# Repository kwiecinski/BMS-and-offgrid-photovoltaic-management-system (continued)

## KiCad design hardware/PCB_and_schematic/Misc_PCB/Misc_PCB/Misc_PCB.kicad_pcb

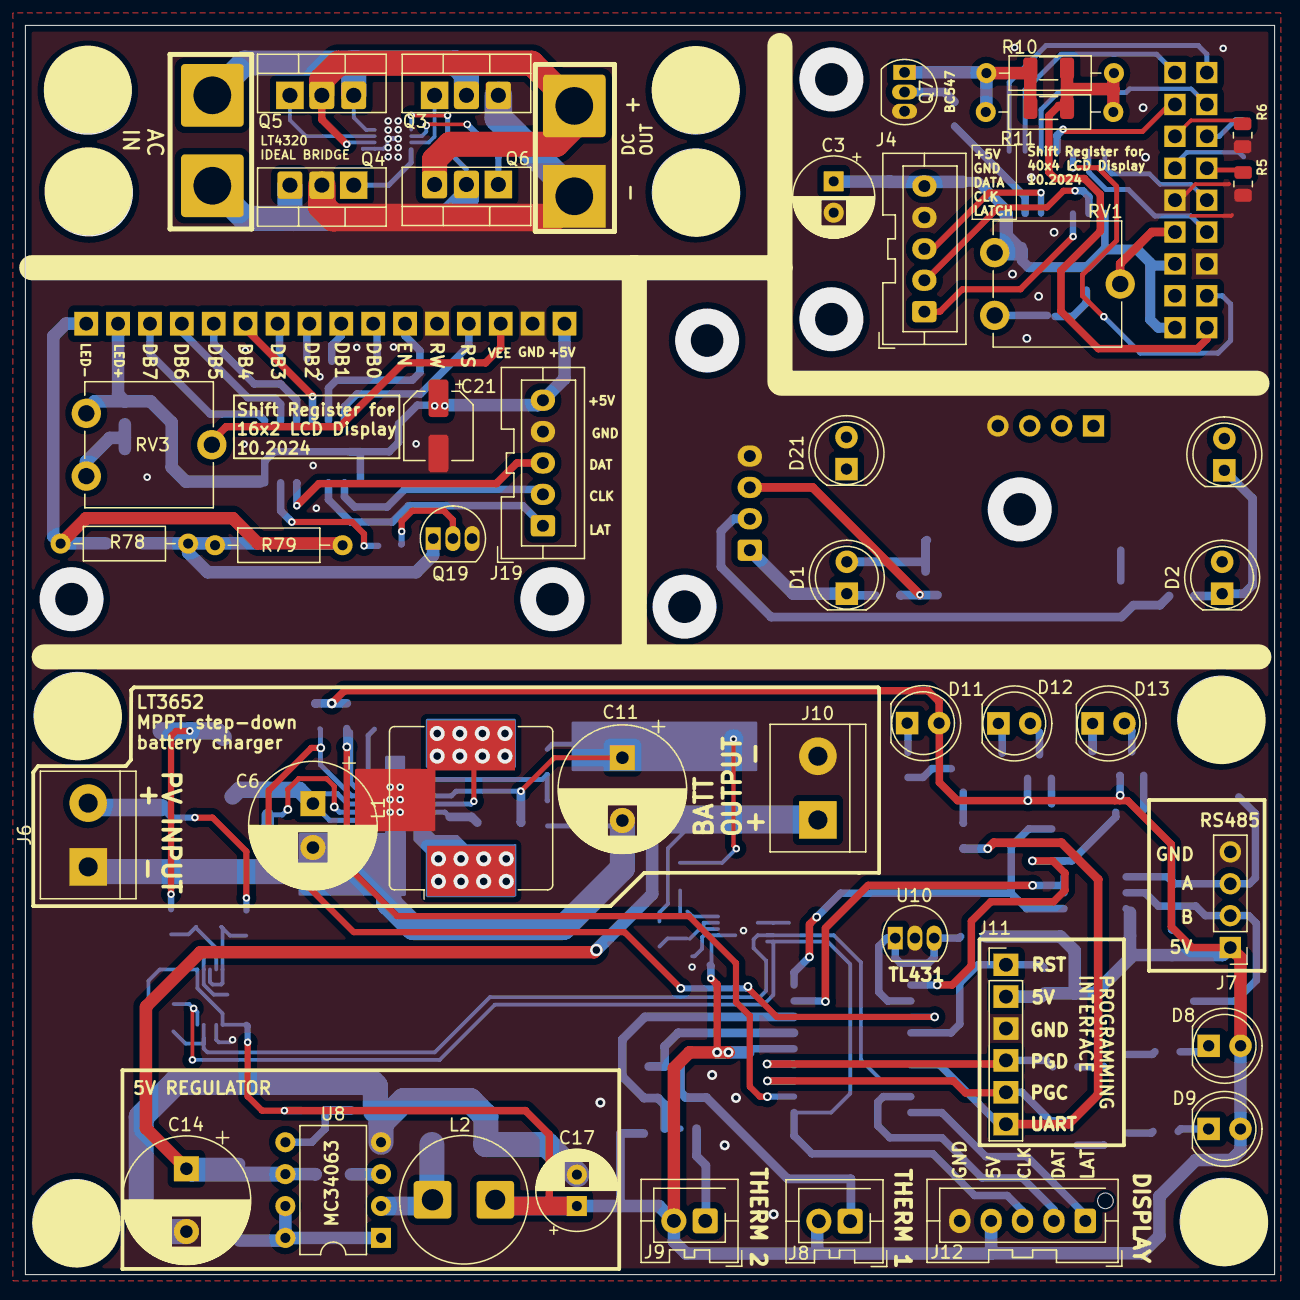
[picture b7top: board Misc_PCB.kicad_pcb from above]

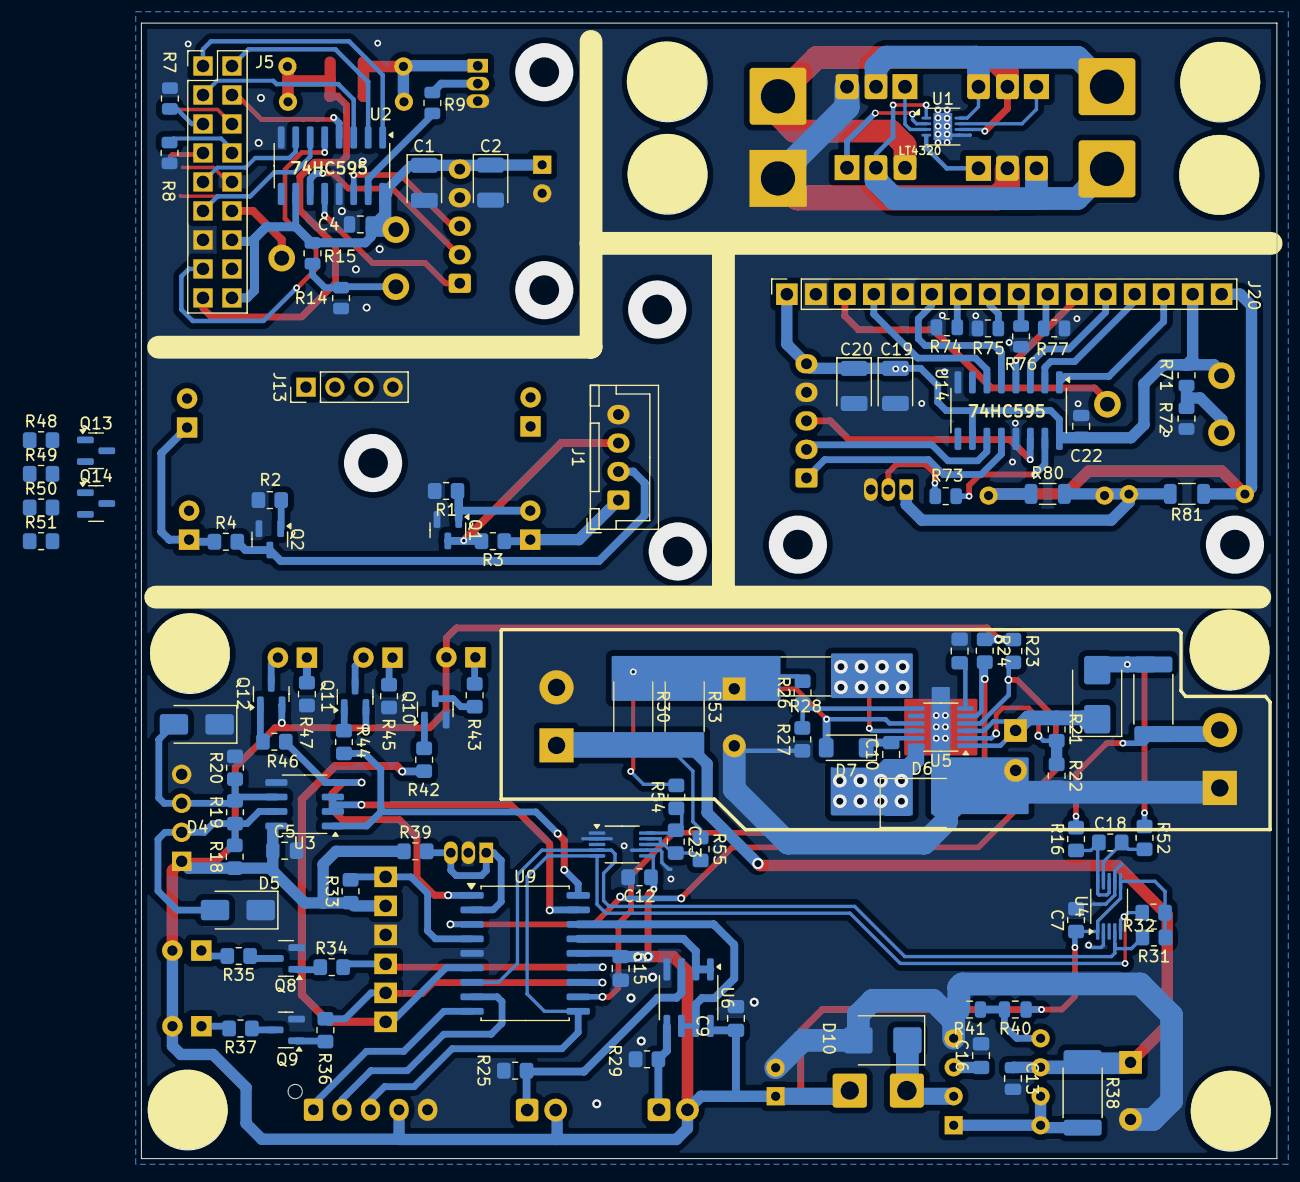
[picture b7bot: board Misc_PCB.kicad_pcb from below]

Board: 2 copper layers, 99.5 x 99.5 mm, 149 parts (103 on the bottom side), 110 nets.

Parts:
C1, C2, C19, C20: 470u/6,3V; CP_EIA-3528-21_Kemet-B
C3: 470u/6,3V; CP_Radial_D6.3mm_P2.50mm
C4, C13, C22: 100n; C_0805_2012Metric
C5, C9, C15: 100n; C_0805_2012Metric_Pad1.18x1.45mm_HandSolder
C6: 470u/40V; CP_Radial_D10.0mm_P3.50mm
C7, C12, C18, C23: 100n; R_0805_2012Metric_Pad1.20x1.40mm_HandSolder
C8: 0R; C_0805_2012Metric_Pad1.18x1.45mm_HandSolder
C10: 1u/10V; C_0805_2012Metric_Pad1.18x1.45mm_HandSolder
C11: 470u/16V; CP_Radial_D10.0mm_P5.00mm
C14: 670u/35V; CP_Radial_D10.0mm_P5.00mm
C16: 100p; C_0805_2012Metric_Pad1.18x1.45mm_HandSolder
C17: 560u/6,3V; CP_Radial_D6.3mm_P2.50mm
C21: 470u/6,3V; CP_Elec_5x5.7
D1, D2, D20, D21: BPV10; LED_D5.0mm
D3, D6, D10: D_Schottky; D_SMB
D4, D5: D_TVS; D_SMA
D7: 1N4148; D_MiniMELF
D8, D9, D11, D12, D13: LED; LED_D5.0mm
J1: DIODE_BLINK_METER; JST_XH_B4B-XH-A_1x04_P2.50mm_Vertical
J2: AC_IN; SolderWire-2.5sqmm_1x02_P7.2mm_D2.4mm_OD3.6mm
J3: DC_OUT; SolderWire-2.5sqmm_1x02_P7.2mm_D2.4mm_OD3.6mm
J4, J19: LCD_CONN; JST_XA_B05B-XASK-1_1x05_P2.50mm_Vertical
J5: LCD_DISPLAY; PinHeader_2x09_P2.54mm_Vertical
J6: SOLAR_PANEL; TerminalBlock_bornier-2_P5.08mm
J7: RS485; PinHeader_1x04_P2.54mm_Vertical
J8, J9: THERMISTOR; JST_XA_B02B-XASK-1-A_1x02_P2.50mm_Vertical
J10: BATT; TerminalBlock_bornier-2_P5.08mm
J11: ICP; PinHeader_1x06_P2.54mm_Vertical
J12: LCD_DISPLAY; JST_XA_B05B-XASK-1-A_1x05_P2.50mm_Vertical
J13: DIODE_BLINK_METER_OUT; PinHeader_1x04_P2.54mm_Vertical
J20: LCD16x2; PinSocket_1x16_P2.54mm_Vertical
L1: L; L_Bourns_SRR1208_12.7x12.7mm
L2: 220uH; L_Radial_D10.0mm_P5.00mm_Fastron_07P
Q1, Q2, Q8, Q9, Q10, Q13, Q14: BC817; SOT-23
Q3, Q4, Q5, Q6: IRF540N; TO-220-3_Vertical-little-bigger pads
Q7, Q19: BC547; TO-92_Inline_LITTLE_BIGGER
Q11, Q12: BC807; SOT-23
R1, R2, R48, R49: 47k; R_0805_2012Metric_Pad1.20x1.40mm_HandSolder
R3, R4, R50, R51: 22k; R_0805_2012Metric_Pad1.20x1.40mm_HandSolder
R5, R6, R7, R8, R9, R15, R71, R73, R74, R75, R76, R77: 10k; R_0805_2012Metric
R10, R11, R78, R79: R; R_Axial_DIN0207_L6.3mm_D2.5mm_P10.16mm_Horizontal
R12, R13, R80, R81: R; R_1206_3216Metric
R14, R72: 39k; R_0805_2012Metric
R16, R52, R54, R55: 10R; R_0805_2012Metric_Pad1.20x1.40mm_HandSolder
R17, R30: 50m; R_2512_6332Metric_Pad1.40x3.35mm_HandSolder
R18, R20, R21, R22: 510R; R_0805_2012Metric_Pad1.20x1.40mm_HandSolder
R19: 120R; R_0805_2012Metric_Pad1.20x1.40mm_HandSolder
R23, R24, R31, R32, R33: 10k; R_0805_2012Metric_Pad1.20x1.40mm_HandSolder
R25, R29: 100K; R_0805_2012Metric_Pad1.20x1.40mm_HandSolder
R26, R27: 100k; R_0805_2012Metric_Pad1.20x1.40mm_HandSolder
R28: 50mR; R_2512_6332Metric_Pad1.40x3.35mm_HandSolder
R34, R36, R42, R44, R46: 10K; R_0805_2012Metric_Pad1.20x1.40mm_HandSolder
R35, R37, R43, R45, R47: 220R; R_0805_2012Metric_Pad1.20x1.40mm_HandSolder
R38: 500m; R_2512_6332Metric_Pad1.40x3.35mm_HandSolder
R39: 1k; R_0805_2012Metric_Pad1.20x1.40mm_HandSolder
R40: 10k; C_0805_2012Metric
R41: 3k3; C_0805_2012Metric
R53: 100m; R_2512_6332Metric_Pad1.40x3.35mm_HandSolder
RV1, RV3: 10k; Potentiometer_ACP_CA9-V10_Vertical
U1: LT4320xDD-1; DFN-8-1EP_3x3mm_P0.5mm_EP1.65x2.38mm
U2, U14: 74HC595; SOIC-16_3.9x9.9mm_P1.27mm
U3: ST485; SOIC-8_3.9x4.9mm_P1.27mm
U4, U7: INA226; VSSOP-10_3x3mm_P0.5mm
U5: LT3652EMSE; MSOP-12-1EP_3x4mm_P0.65mm_EP1.65x2.85mm
U6: LM358; SOIC-8_3.9x4.9mm_P1.27mm
U8: MC34063AP; DIP-8_W7.62mm
U9: PIC16F819-ISO; SOIC-18W_7.5x11.6mm_P1.27mm
U10: TL431LP; TO-92_Inline_LITTLE_BIGGER

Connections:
+5V: C1.1, C2.1, C3.1, C4.1, C5.1, C7.1, C9.1, C12.1, C15.1, C17.1, C19.1, C20.1, C21.1, C22.1, D1.1 (K), D2.1 (K), D8.2 (A), D9.2 (A), D11.2 (A), D20.1 (K), D21.1 (K), J1.1, J4.5, J5.14, J5.18, J7.1, J8.2, J9.2, J11.2, J12.4, J13.1, J19.5, J20.1, J20.15, L2.2, Q11.2 (E), Q12.2 (E), R3.1, R4.1, R15.2, R18.1, R23.1, R24.1, R31.1, R32.1, R33.1, R39.1, R40.1, R50.1, R51.1, R71.2, RV1.3, RV3.3, U2.10 (~SRCLR), U2.16 (VCC), U3.8 (VCC), U4.1 (A1), U4.6 (VS), U6.8 (V+), U7.6 (VS), U9.14 (VDD), U14.10 (~SRCLR), U14.16 (VCC)
/LT3652 MPPT/RS485_A: D4.2 (A2), J7.3, R19.2, R20.1, U3.6 (A)
/LT3652 MPPT/RS485_B: D5.2 (A2), J7.2, R18.2, R19.1, U3.7 (B)
/Shift Register for 16x2 LCD Display/CLK: J19.2, U14.11 (SRCLK)
/Shift Register for 16x2 LCD Display/DATA: J19.3, U14.14 (SER)
/Shift Register for 16x2 LCD Display/LATCH: J19.1, U14.12 (RCLK)
/Shift Register for 40x4 LCD Display/CLK: J4.2, U2.11 (SRCLK)
/Shift Register for 40x4 LCD Display/DATA: J4.3, U2.14 (SER)
/Shift Register for 40x4 LCD Display/LATCH: J4.1, U2.12 (RCLK)
BACKLIGHT_DRIVE: R9.1, U2.15 (QA)
BACKLIGHT_DRIVE_A: R73.1, U14.15 (QA)
BATT_CURRENT_HIGH: C11.1, D7.2 (A), R26.2, R28.2, R30.1, R53.1, R54.2, U5.9 (BAT)
BATT_CURRENT_LOW: C13.1, C14.1, J10.1, R30.2, R38.1, R53.2, R55.1, U8.6 (Vin)
CHRG: R23.2, U5.4 (~CHRG), U9.3 (T0CKL/AN4/RA4)
DATA: J12.2, U9.8 (RB2/SDO/CCP1)
DB0: J5.8, R8.2
DB1: J5.7, R5.2
DB2: J5.6, R6.2
DB3: J5.5, R7.2
DB4: J5.4, U2.4 (QE)
DB4_A: J20.11, U14.4 (QE)
DB5: J5.3, U2.3 (QD)
DB5_A: J20.12, U14.3 (QD)
DB6: J5.2, U2.2 (QC)
DB6_A: J20.13, U14.2 (QC)
DB7: J5.1, U2.1 (QB)
DB7_A: J20.14, U14.1 (QB)
DBG_UART: J11.6, R42.2, U9.6 (RB0/INT)
E1: J5.9, U2.7 (QH)
E2: J5.15, U2.5 (QF)
EN: J20.6, U14.5 (QF)
FAULT: R24.2, U5.5 (~FAULT), U9.11 (RB5/~SS)
GND: C1.2, C2.2, C3.2, C4.2, C5.2, C6.2, C7.2, C8.2, C9.2, C11.2, C12.2, C13.2, C14.2, C15.2, C16.2, C17.2, C19.2, C20.2, C21.2, C22.2, D4.1 (A1), D5.1 (A1), D6.2 (A), D10.2 (A), J1.4, J3.2, J4.4, J5.10, J5.13, J6.1, J7.4, J10.2, J11.3, J12.5, J13.4, J19.4, J20.2, J20.5, Q1.2 (E), Q2.2 (E), Q3.3 (S), Q4.2 (D), Q7.3 (E), Q8.2 (E), Q9.2 (E), Q10.2 (E), Q13.2 (E), Q14.2 (E), Q19.3 (E), R1.2, R2.2, R5.1, R6.1, R7.1, R8.1, R14.2, R20.2, R22.2, R25.2, R27.1, R29.2, R41.2, R45.1, R47.1, R48.2, R49.2, R72.2, R74.1, R75.1, R76.1, R77.1, U1.5 (OUTN), U1.9 (OUTN), U2.8 (GND), U2.13 (~OE), U3.5 (GND), U4.2 (A0), U4.7 (GND), U5.13 (GND), U6.4 (V-), U7.1 (A1), U7.2 (A0), U7.7 (GND), U8.4 (GND), U9.5 (VSS), U10.2 (A), U14.8 (GND), U14.13 (~OE)
LATCH: J12.1, U9.9 (RB3/CCP1/PGM)
unnamed: D1.2 (A), Q1.1 (B), R1.1
unnamed: D2.2 (A), Q2.1 (B), R2.1
unnamed: C6.1, D3.1 (K), R21.1, U5.1 (V_{IN}), U5.3 (~SHDN)
unnamed: C10.1, D6.1 (K), L1.1, U5.12 (SW)
unnamed: C10.2, D7.1 (K), U5.11 (BOOST)
unnamed: D8.1 (K), R35.2
unnamed: D9.1 (K), R37.2
unnamed: D10.1 (K), L2.1, U8.2 (SwE)
unnamed: D11.1 (K), R43.2
unnamed: D12.2 (A), Q11.3 (C)
unnamed: D12.1 (K), R45.2
unnamed: D13.2 (A), Q12.3 (C)
unnamed: D13.1 (K), R47.2
unnamed: D20.2 (A), Q13.1 (B), R48.1
unnamed: D21.2 (A), Q14.1 (B), R49.1
unnamed: J1.2, Q2.3 (C), R4.2
unnamed: J1.3, Q1.3 (C), R3.2
unnamed: J2.1, Q4.3 (S), Q6.2 (D), U1.1 (IN2)
unnamed: J2.2, Q3.2 (D), Q5.3 (S), U1.8 (IN1)
unnamed: J3.1, Q5.2 (D), Q6.3 (S), U1.6 (OUTP)
unnamed: J5.12, RV1.2
unnamed: J5.17, R10.1, R11.1, R12.1, R13.1
unnamed: J8.1, R25.1, U6.3 (+)
unnamed: J9.1, R29.1, U6.5 (+)
unnamed: J13.2, Q14.3 (C), R51.2
unnamed: J13.3, Q13.3 (C), R50.2
unnamed: J20.3, RV3.2
unnamed: J20.7, R74.2
unnamed: J20.8, R75.2
unnamed: J20.9, R76.2
unnamed: J20.10, R77.2
unnamed: J20.16, R78.1, R79.1, R80.1, R81.1
unnamed: Q3.1 (G), U1.3 (BG2)
unnamed: Q4.1 (G), U1.4 (BG1)
unnamed: Q5.1 (G), U1.7 (TG1)
unnamed: Q6.1 (G), U1.2 (TG2)
unnamed: Q7.2 (B), R9.2
unnamed: Q7.1 (C), R10.2, R11.2, R12.2, R13.2
unnamed: Q8.1 (B), R34.1
unnamed: Q8.3 (C), R35.1
unnamed: Q9.1 (B), R36.1
unnamed: Q9.3 (C), R37.1
unnamed: Q10.1 (B), R42.1
unnamed: Q10.3 (C), R43.1
unnamed: Q11.1 (B), R44.1
unnamed: Q12.1 (B), R46.1
unnamed: Q19.2 (B), R73.2
unnamed: Q19.1 (C), R78.2, R79.2, R80.2, R81.2
unnamed: R14.1, R15.1, RV1.1
unnamed: R71.1, R72.1, RV3.1
unnamed: C18.1, R16.1, U4.8 (Vbus), U4.10 (Vin+)
unnamed: C18.2, R52.2, U4.9 (Vin-)
unnamed: L1.2, R28.1, U5.10 (SENSE)
unnamed: C8.1, U5.6 (TIMER)
unnamed: R26.1, R27.2, U5.7 (V_{FB})
unnamed: R21.2, R22.1, U5.2 (V_{IN_REG})
unnamed: C23.2, R55.2, U7.8 (Vbus), U7.9 (Vin-)
unnamed: C23.1, R54.1, U7.10 (Vin+)
unnamed: R38.2, U8.1 (SwC), U8.7 (Ipk), U8.8 (DC)
unnamed: C16.1, U8.3 (TC)
unnamed: R40.2, R41.1, U8.5 (Vfb)
PGC: J11.5, R36.2, U9.12 (RB6/T1OSO/T1CKI/PGC)
PGD: J11.4, R34.2, U9.13 (RB7/T1OSI/PGD)
RS: J5.11, U2.6 (QG)
RS232_RX: R44.2, U3.1 (RO), U9.18 (AN1/RA1)
RS232_TX: R46.2, U3.4 (DI), U9.1 (Vref-/AN2/RA2)
RS485_OUTPUT_ENABLE: U3.2 (~RE), U3.3 (DE), U9.17 (AN0/RA0)
RST: J11.1, R33.2, U9.4 (Vpp/~MCLR/RA5)
RS_A: J20.4, U14.6 (QG)
SCL_SCK: J12.3, R32.2, U4.5 (SCL), U7.5 (SCL), U9.10 (RB4/SCK/SCL)
SDA: R31.2, U4.4 (SDA), U7.4 (SDA), U9.7 (RB1/SDI/SDA)
SOLAR_CURRENT_HIGH: J6.2, R16.2, R17.1
SOLAR_CURRENT_LOW: D3.2 (A), R17.2, R52.1
TEMP1: U6.1, U6.2 (-), U9.15 (CLKO/OSC2/RA6)
TEMP2: U6.6 (-), U6.7, U9.16 (CLKI/OSC1/RA7)
VREF_2V5: R39.2, U9.2 (Vref+/AN3/RA3), U10.1 (REF), U10.3 (K)

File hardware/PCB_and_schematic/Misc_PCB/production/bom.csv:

Designator,Footprint,Quantity,Value,LCSC Part #
"C1, C19, C2, C20",CP_EIA-3528-21_Kemet-B,4,"470u/6,3V",
C10,0805,1,1u/10V,
C11,CP_Radial_D10.0mm_P5.00mm,1,470u/16V,
"C12, C13, C15, C18, C22, C23, C4, C5, C7, C9",0805,10,100n,
C14,CP_Radial_D10.0mm_P5.00mm,1,670u/35V,
C16,0805,1,100p,
C17,CP_Radial_D6.3mm_P2.50mm,1,"560u/6,3V",
C21,CP_Elec_5x5.7,1,"470u/6,3V",
C3,CP_Radial_D6.3mm_P2.50mm,1,"470u/6,3V",
C6,CP_Radial_D10.0mm_P3.50mm,1,470u/40V,
C8,0805,1,0R,
"D1, D2, D20, D21",LED_D5.0mm,4,BPV10,
"D10, D3, D6",D_SMB,3,D_Schottky,
"D11, D12, D13, D8, D9",LED_D5.0mm,5,LED,
"D4, D5",D_SMA,2,D_TVS,
D7,D_MiniMELF,1,1N4148,
J1,JST_XH_B4B-XH-A_1x04_P2.50mm_Vertical,1,DIODE_BLINK_METER,
J10,TerminalBlock_bornier-2_P5.08mm,1,BATT,
J11,PinHeader_1x06_P2.54mm_Vertical,1,ICP,
J12,JST_XA_B05B-XASK-1-A_1x05_P2.50mm_Vertical,1,LCD_DISPLAY,
J13,PinHeader_1x04_P2.54mm_Vertical,1,DIODE_BLINK_METER_OUT,
"J19, J4",JST_XA_B05B-XASK-1_1x05_P2.50mm_Vertical,2,LCD_CONN,
J2,SolderWire-2.5sqmm_1x02_P7.2mm_D2.4mm_OD3.6mm,1,AC_IN,
J20,PinSocket_1x16_P2.54mm_Vertical,1,LCD16x2,
J3,SolderWire-2.5sqmm_1x02_P7.2mm_D2.4mm_OD3.6mm,1,DC_OUT,
J5,PinHeader_2x09_P2.54mm_Vertical,1,LCD_DISPLAY,
J6,TerminalBlock_bornier-2_P5.08mm,1,SOLAR_PANEL,
J7,PinHeader_1x04_P2.54mm_Vertical,1,RS485,
"J8, J9",JST_XA_B02B-XASK-1-A_1x02_P2.50mm_Vertical,2,THERMISTOR,
L1,L_Bourns_SRR1208_12.7x12.7mm,1,L,
L2,L_Radial_D10.0mm_P5.00mm_Fastron_07P,1,220uH,
"Q1, Q10, Q13, Q14, Q2, Q8, Q9",SOT-23,7,BC817,
"Q11, Q12",SOT-23,2,BC807,
"Q19, Q7",TO-92_Inline_LITTLE_BIGGER,2,BC547,
"Q3, Q4, Q5, Q6",TO-220-3_Vertical-little-bigger pads,4,IRF540N,
"R1, R2, R48, R49",0805,4,47k,
"R10, R11, R78, R79",R_Axial_DIN0207_L6.3mm_D2.5mm_P10.16mm_Horizontal,4,R,
"R12, R13, R80, R81",1206,4,R,
"R14, R72",0805,2,39k,
"R15, R23, R24, R31, R32, R33, R34, R36, R40, R42, R44, R46, R5, R6, R7, R71, R73, R74, R75, R76, R77, R8, R9",0805,23,10k,
"R16, R52, R54, R55",0805,4,10R,
"R17, R30",2512,2,50m,
"R18, R20, R21, R22",0805,4,510R,
R19,0805,1,120R,
"R25, R26, R27, R29",0805,4,100K,
R28,2512,1,50mR,
"R3, R4, R50, R51",0805,4,22k,
"R35, R37, R43, R45, R47",0805,5,220R,
R38,2512,1,500m,
R39,0805,1,1k,
R41,0805,1,3k3,
R53,2512,1,100m,
"RV1, RV3",Potentiometer_ACP_CA9-V10_Vertical,2,10k,
U1,DFN-8-1EP_3x3mm_P0.5mm_EP1.65x2.38mm,1,LT4320xDD-1,
U10,TO-92_Inline_LITTLE_BIGGER,1,TL431LP,
"U14, U2",SOIC-16_3.9x9.9mm_P1.27mm,2,74HC595,
U3,SOIC-8_3.9x4.9mm_P1.27mm,1,ST485,
"U4, U7",VSSOP-10_3x3mm_P0.5mm,2,INA226,
U5,MSOP-12-1EP_3x4mm_P0.65mm_EP1.65x2.85mm,1,LT3652EMSE,
U6,SOIC-8_3.9x4.9mm_P1.27mm,1,LM358,
U8,DIP-8_W7.62mm,1,MC34063AP,
U9,SOIC-18W_7.5x11.6mm_P1.27mm,1,PIC16F819-ISO,

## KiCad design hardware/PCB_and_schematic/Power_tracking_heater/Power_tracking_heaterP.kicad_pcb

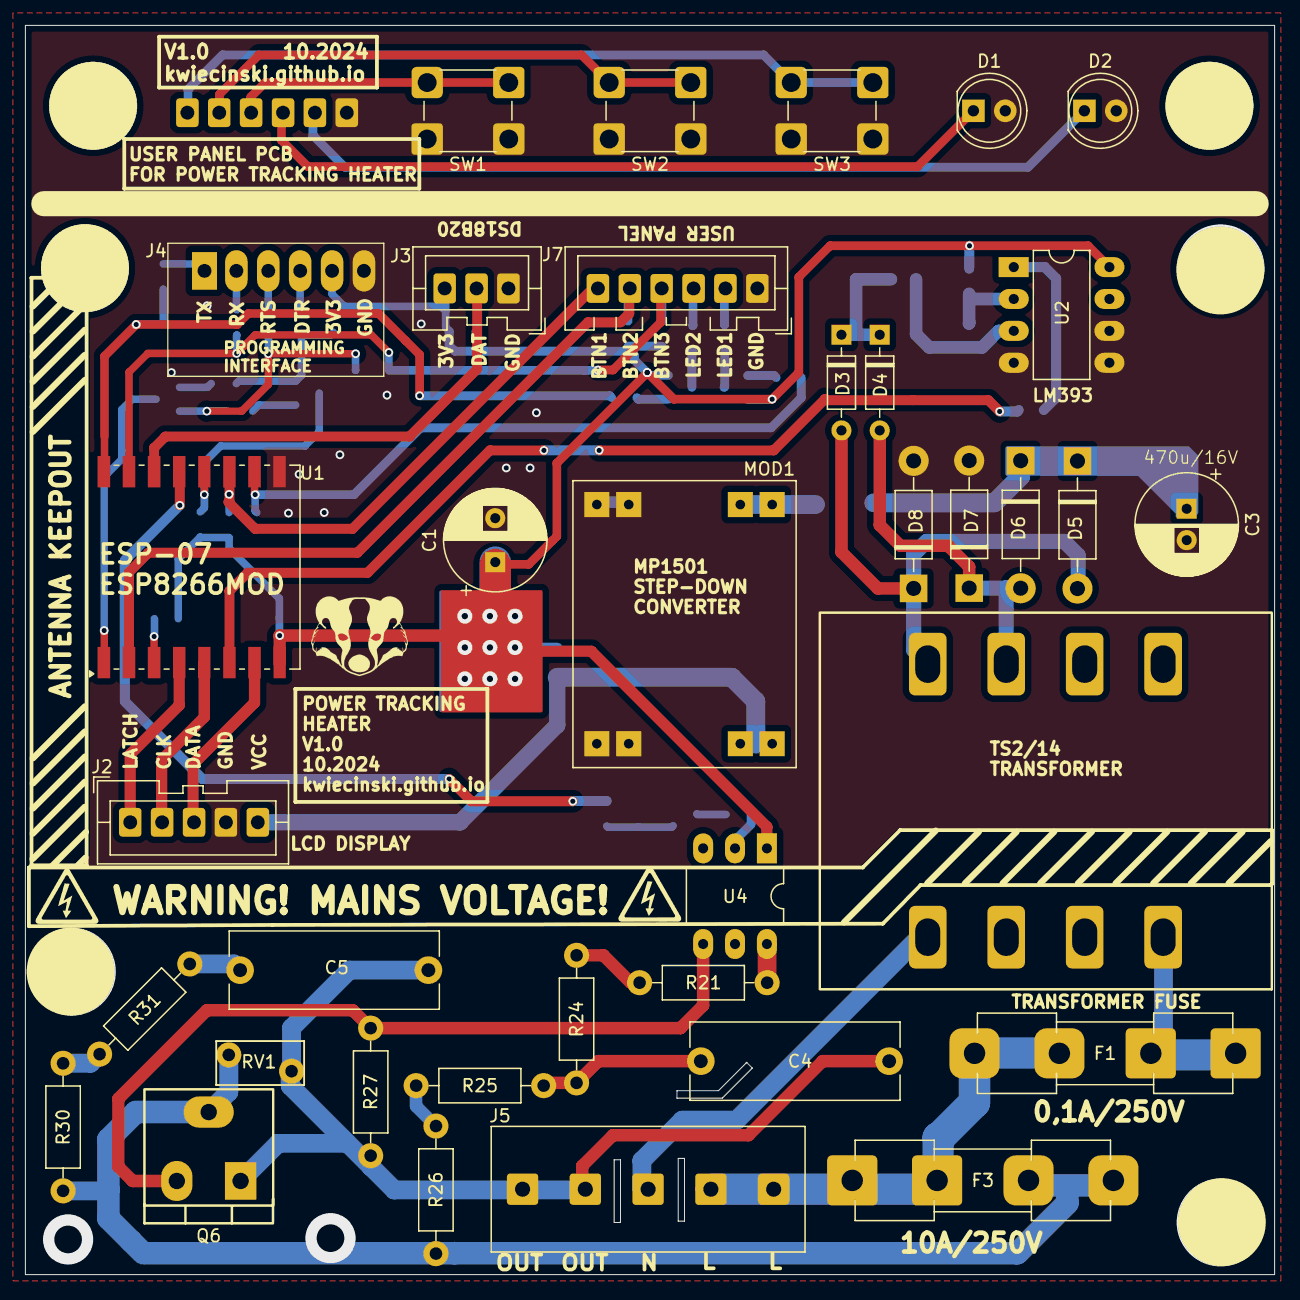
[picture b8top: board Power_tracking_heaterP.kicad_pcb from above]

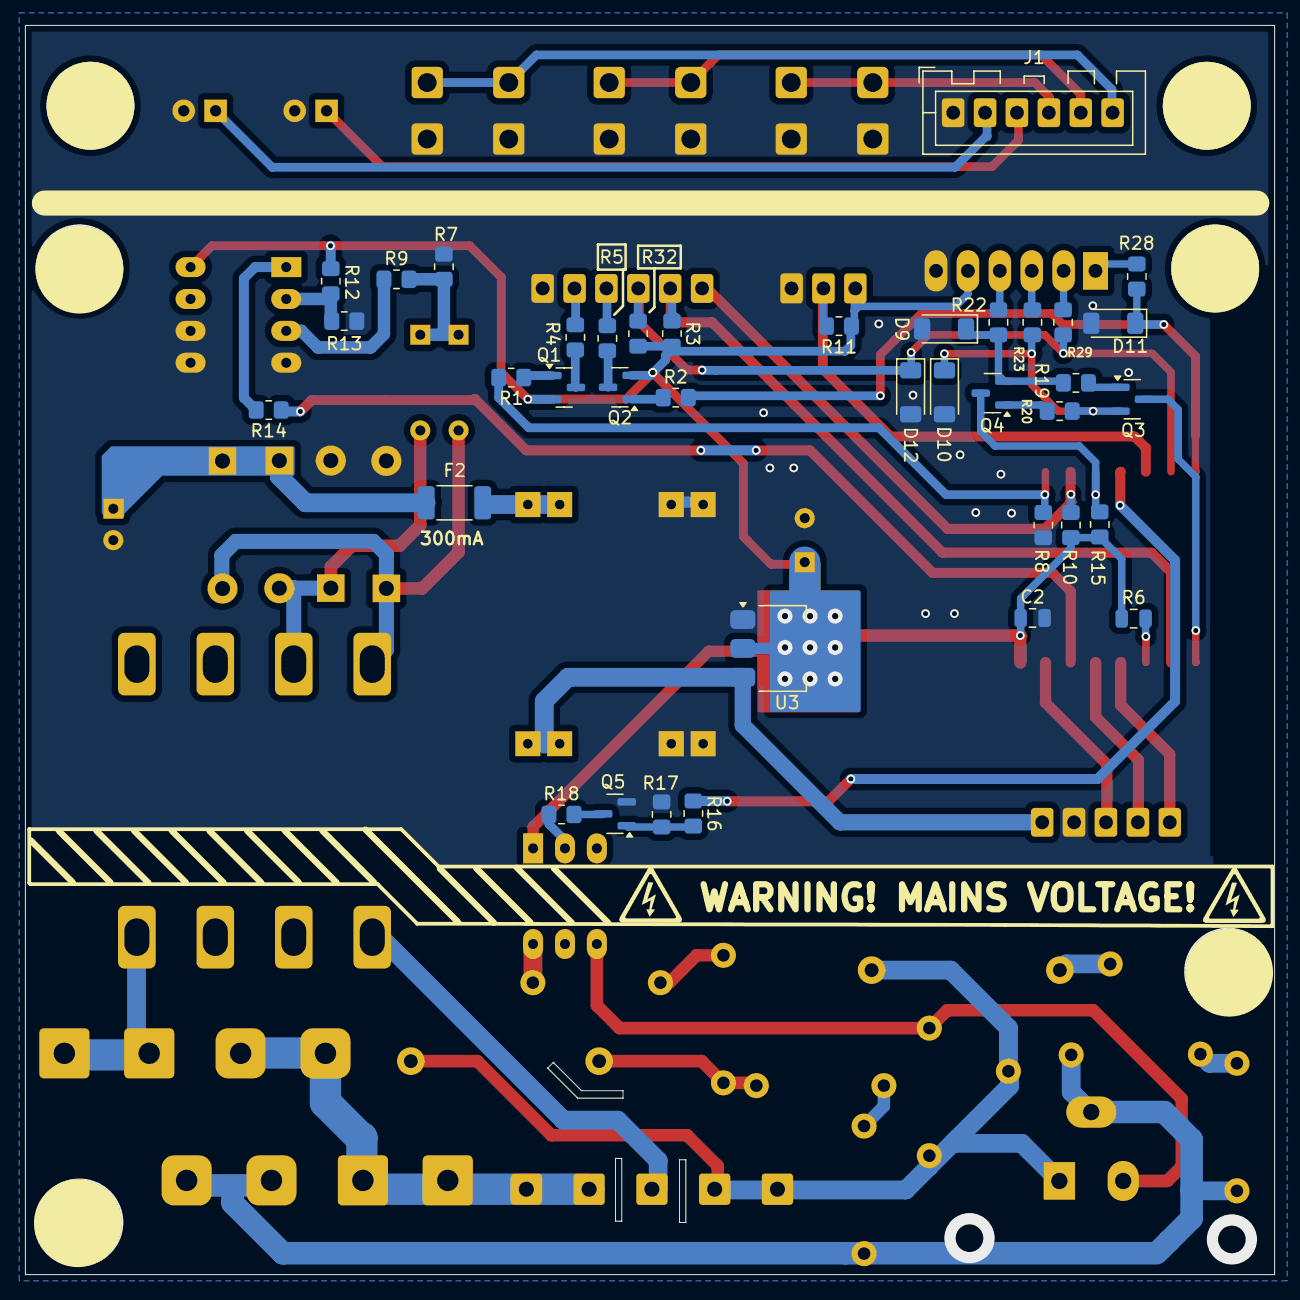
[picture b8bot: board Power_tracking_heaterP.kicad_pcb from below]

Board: 2 copper layers, 99.5 x 99.5 mm, 74 parts (38 on the bottom side), 59 nets.

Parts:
C1: 470u/6,3V; CP_Radial_D8.0mm_P3.50mm
C2: 100n; C_0805_2012Metric
C3: 470u/16V; CP_Radial_D8.0mm_P2.50mm
C4: 22n/250V AC; C_Rect_L16.5mm_W6.0mm_P15.00mm_MKT
C5: 10n/250V; C_Rect_L16.5mm_W6.0mm_P15.00mm_MKT
D1, D2: LED; LED_D5.0mm
D3, D4: 1N4148; D_DO-35_SOD27_P7.62mm_Horizontal
D5, D6, D7, D8: 1N4007; DO-41_SOD81_P10.16mm_Horizontal
D9, D10, D11, D12: 3V3; D_MiniMELF
F1: 100mA/250V; Fuseholder_Clip-5x20mm_Eaton_1A5601-01_Inline_P20.80x6.76mm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
F2: 300mA; Fuse_2010_5025Metric
F3: 10A/250V; Fuseholder_Clip-5x20mm_Eaton_1A5601-01_Inline_P20.80x6.76mm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
J1, J7: USER_PANEL; JST_XH_1x06_P2.54mm_Vertical
J2: DISPLAY; JST_XA_1x05_P2.50mm_Vertical
J3: DS18B20; JST_XA_1x03_P2.54mm_Vertical
J4: PROG_INTERFACE; Conn-01x06
J5: POWER_OUTPUT; Screw-Terminal-5.00mm-5pin
MOD1: LM2596-Step-Down; MP1504_Mini_3A_Step_Down_Conv
Q1, Q2: BC807; SOT-23
Q3, Q4, Q5: BC817; SOT-23
Q6: BT139-600; TO-220-3_V_Wide_Legs
R1, R2: 10K; R_0805_2012Metric_Pad1.20x1.40mm_HandSolder
R3, R7, R8, R9, R10, R11, R14, R15, R16, R19, R20, R32: 10k; R_0805_2012Metric_Pad1.20x1.40mm_HandSolder
R4, R5: 220R; R_0805_2012Metric_Pad1.20x1.40mm_HandSolder
R6: 10k; C_0805_2012Metric
R12: 33k; R_0805_2012Metric_Pad1.20x1.40mm_HandSolder
R13, R28, R29: 1k; R_0805_2012Metric_Pad1.20x1.40mm_HandSolder
R17: 47k; R_0805_2012Metric_Pad1.20x1.40mm_HandSolder
R18: 47R; R_0805_2012Metric_Pad1.20x1.40mm_HandSolder
R21, R24, R25, R26: 200R; R_Axial_DIN0207_L6.3mm_D2.5mm_P10.16mm_Horizontal
R22, R23: 560R; R_0805_2012Metric_Pad1.20x1.40mm_HandSolder
R27: R_Axial_DIN0207_L6.3mm_D2.5mm_P10.16mm_Horizontal
R30, R31: 50R; R_Axial_DIN0207_L6.3mm_D2.5mm_P10.16mm_Horizontal
RV1: S10K275; RV_Disc_D7mm_W3.5mm_P5mm
SW1, SW2, SW3: SW_Push; SW_PUSH_6mm
T1: Transformer_1P_1S; Transformer TS2-14
U1: ESP-07
U2: LM393; DIP-8_W7.62mm_LongPads
U3: AMS1117-3.3; SOT-223-3_TabPin2
U4: MOC3033M; DIP-6_W7.62mm_LongPads

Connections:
230V_L: F1.1, F3.2, J5.1, J5.2
230V_N: J5.3, T1.4 (AB)
+3V3: C1.1, C2.1, J3.3, J4.5, Q1.2 (E), Q2.2 (E), R3.2, R6.1, R10.2, R11.1, R12.1, R15.1, R32.2, U1.8 (VCC), U2.8 (V+), U3.2 (VO), U4.1
+5V: J2.5, MOD1.4 (OUT+), U3.3 (VI)
AC_POWER_DRIVE: R16.1, U1.13 (GPIO4)
AC_SEC_1: D3.2 (A), D5.2 (A), D8.1 (K), T1.8 (SB)
AC_SEC_2: D4.2 (A), D6.2 (A), D7.1 (K), T1.7 (SA)
CLK: J2.2, U1.5 (GPIO14)
CS: J2.1, U1.4 (GPIO16)
DS18B20: J3.2, R11.2, U1.14 (GPIO5)
DTR: J4.4, R22.2
GND: C1.2, C2.2, C3.2, D1.2 (K), D2.2 (K), D7.2 (A), D8.2 (A), D9.2 (A), D10.2 (A), D11.2 (A), D12.2 (A), J1.1, J2.4, J3.1, J4.6, J7.1, MOD1.1 (IN-), MOD1.3 (OUT-), Q5.2 (E), R7.2, R8.2, R13.2, R17.1, SW1.1, SW2.1, SW3.1, U1.9 (GND), U2.4 (V-), U2.5 (+), U2.6 (-), U3.1 (GND)
GPIO0: Q4.3 (C), R15.2, U1.12 (GPIO0)
LED_1: R1.2, R8.1, U1.10 (GPIO15)
LED_1_OUT: J7.2, R4.1
LED_2_OUT: J7.3, R5.1
MOSI: J2.3, U1.7 (GPIO13)
unnamed: C4.1, R24.1, R25.2
unnamed: C5.1, R31.2
unnamed: D1.1 (A), J1.3
unnamed: D2.1 (A), J1.2
unnamed: D3.1 (K), D4.1 (K), R7.1, R9.2
unnamed: C3.1, D5.1 (K), D6.1 (K), F2.1
unnamed: D9.1 (K), Q4.2 (E), R19.2, R22.1
unnamed: D10.1 (K), Q3.2 (E), R20.2, R23.1
unnamed: J1.4, SW1.2
unnamed: J1.5, SW2.2
unnamed: J1.6, SW3.2
unnamed: J4.1, R28.2
unnamed: J4.2, R29.2
unnamed: C4.2, C5.2, J5.4, J5.5, Q6.1 (A1), R27.2, RV1.1
unnamed: F2.2, MOD1.2 (IN+)
unnamed: Q1.1 (B), R1.1
unnamed: Q1.3 (C), R4.2
unnamed: Q2.1 (B), R2.1
unnamed: Q2.3 (C), R5.2
unnamed: Q3.1 (B), R19.1
unnamed: Q4.1 (B), R20.1
unnamed: Q5.1 (B), R16.2, R17.2
unnamed: Q5.3 (C), R18.2
unnamed: F3.1, Q6.2 (A2), R26.1, R30.1, RV1.2
unnamed: Q6.3 (G), R27.1, U4.4
unnamed: R14.2, U2.1
unnamed: R18.1, U4.2
unnamed: R21.1, R24.2
unnamed: R21.2, U4.6
unnamed: R25.1, R26.2
unnamed: R30.2, R31.1
unnamed: F1.2, T1.1 (AA)
unnamed: R6.2, U1.3 (EN)
unnamed: R9.1, U2.3 (+)
unnamed: R12.2, R13.1, U2.2 (-)
PUSH_BUTTON_1: J7.6, R10.1, U1.11 (GPIO2)
PUSH_BUTTON_2: J7.5, R3.1, U1.2 (ADC)
RST: Q3.3 (C), U1.1 (~RST)
RTS: J4.3, R23.2
RXD_PUSH_BUTTON_3: D12.1 (K), J7.4, R29.1, R32.1, U1.15 (GPIO3/RXD)
TXD_LED2: D11.1 (K), R2.2, R28.1, U1.16 (GPIO1/TXD)
ZERO_CROSSING_SIGNAL: R14.1, U1.6 (GPIO12)

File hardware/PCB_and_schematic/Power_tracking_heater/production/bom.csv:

Designator,Footprint,Quantity,Value,LCSC Part #
C1,CP_Radial_D8.0mm_P3.50mm,1,"470u/6,3V",
C2,0805,1,100n,
C3,CP_Radial_D8.0mm_P2.50mm,1,470u/16V,
C4,C_Rect_L16.5mm_W6.0mm_P15.00mm_MKT,1,22n/250V AC,
C5,C_Rect_L16.5mm_W6.0mm_P15.00mm_MKT,1,10n/250V,
"D1, D2",LED_D5.0mm,2,LED,
"D10, D11, D12, D9",D_MiniMELF,4,3V3,
"D3, D4",D_DO-35_SOD27_P7.62mm_Horizontal,2,1N4148,
"D5, D6, D7, D8",DO-41_SOD81_P10.16mm_Horizontal,4,1N4007,
F1,Fuseholder_Clip-5x20mm_Eaton_1A5601-01_Inline_P20.80x6.76mm_D1.70mm_Horizontal,1,100mA/250V,
F2,2010,1,300mA,
F3,Fuseholder_Clip-5x20mm_Eaton_1A5601-01_Inline_P20.80x6.76mm_D1.70mm_Horizontal,1,10A/250V,
"J1, J7",JST_XH_1x06_P2.54mm_Vertical,2,USER_PANEL,
J2,JST_XA_1x05_P2.50mm_Vertical,1,DISPLAY,
J3,JST_XA_1x03_P2.54mm_Vertical,1,DS18B20,
J4,Conn-01x06,1,PROG_INTERFACE,
J5,Screw-Terminal-5.00mm-5pin,1,POWER_OUTPUT,
MOD1,MP1504_Mini_3A_Step_Down_Conv,1,LM2596-Step-Down,
"Q1, Q2",SOT-23,2,BC807,
"Q3, Q4, Q5",SOT-23,3,BC817,
Q6,TO-220-3_V_Wide_Legs,1,BT139-600,
"R1, R10, R11, R14, R15, R16, R19, R2, R20, R3, R32, R6, R7, R8, R9",0805,15,10K,
R12,0805,1,33k,
"R13, R28, R29",0805,3,1k,
R17,0805,1,47k,
R18,0805,1,47R,
"R21, R24, R25, R26",R_Axial_DIN0207_L6.3mm_D2.5mm_P10.16mm_Horizontal,4,200R,
"R22, R23",0805,2,560R,
R27,R_Axial_DIN0207_L6.3mm_D2.5mm_P10.16mm_Horizontal,1,~,
"R30, R31",R_Axial_DIN0207_L6.3mm_D2.5mm_P10.16mm_Horizontal,2,50R,
"R4, R5",0805,2,220R,
RV1,RV_Disc_D7mm_W3.5mm_P5mm,1,S10K275,
"SW1, SW2, SW3",SW_PUSH_6mm,3,SW_Push,
T1,Transformer TS2-14,1,Transformer_1P_1S,
U1,ESP-07,1,ESP-07,
U2,DIP-8_W7.62mm_LongPads,1,LM393,
U3,SOT-223-3_TabPin2,1,AMS1117-3.3,
U4,DIP-6_W7.62mm_LongPads,1,MOC3033M,

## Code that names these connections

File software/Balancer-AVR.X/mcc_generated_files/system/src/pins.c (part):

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}

/**
  Allows selecting an interrupt handler for PC3 at application runtime
*/
void PC3_SetInterruptHandler(void (* interruptHandler)(void)) 
{
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
void PC3_DefaultInterruptHandler(void)
{
    // add your PC3 interrupt custom code
    // or set custom function using PC3_SetInterruptHandler()
}
/**
  Allows selecting an interrupt handler for PC2 at application runtime
*/
void PC2_SetInterruptHandler(void (* interruptHandler)(void)) 
{
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
void PC2_DefaultInterruptHandler(void)
{
    // add your PC2 interrupt custom code
    // or set custom function using PC2_SetInterruptHandler()
}
/**
  Allows selecting an interrupt handler for PF0 at application runtime
*/
void PF0_SetInterruptHandler(void (* interruptHandler)(void)) 
{
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
void PF0_DefaultInterruptHandler(void)
{
    // add your PF0 interrupt custom code
    // or set custom function using PF0_SetInterruptHandler()
}
/**
  Allows selecting an interrupt handler for PF1 at application runtime
*/
void PF1_SetInterruptHandler(void (* interruptHandler)(void)) 
{
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
void PF1_DefaultInterruptHandler(void)
{
    // add your PF1 interrupt custom code
    // or set custom function using PF1_SetInterruptHandler()
}
/**
  Allows selecting an interrupt handler for PA4 at application runtime
*/
void PA4_SetInterruptHandler(void (* interruptHandler)(void)) 
{
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
void PA4_DefaultInterruptHandler(void)
{
    // add your PA4 interrupt custom code
    // or set custom function using PA4_SetInterruptHandler()
}
/**
  Allows selecting an interrupt handler for PA5 at application runtime
*/
void PA5_SetInterruptHandler(void (* interruptHandler)(void)) 
{
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
void PA5_DefaultInterruptHandler(void)
{
    // add your PA5 interrupt custom code
    // or set custom function using PA5_SetInterruptHandler()
}
/**
  Allows selecting an interrupt handler for PD4 at application runtime
*/
void PD4_SetInterruptHandler(void (* interruptHandler)(void)) 
{
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
void PD4_DefaultInterruptHandler(void)
{
    // add your PD4 interrupt custom code
    // or set custom function using PD4_SetInterruptHandler()
}
/**
  Allows selecting an interrupt handler for PD5 at application runtime
*/
void PD5_SetInterruptHandler(void (* interruptHandler)(void)) 
{
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
void PD5_DefaultInterruptHandler(void)
{
    // add your PD5 interrupt custom code
    // or set custom function using PD5_SetInterruptHandler()
}
/**
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    // or set custom function using PA6_SetInterruptHandler()
}
/**
  Allows selecting an interrupt handler for PA7 at application runtime
*/
void PA7_SetInterruptHandler(void (* interruptHandler)(void)) 
{
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
void PA7_DefaultInterruptHandler(void)
{
    // add your PA7 interrupt custom code
    // or set custom function using PA7_SetInterruptHandler()
}
/**
  Allows selecting an interrupt handler for PC1 at application runtime
*/
void PC1_SetInterruptHandler(void (* interruptHandler)(void)) 
{
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
void PC1_DefaultInterruptHandler(void)
{
    // add your PC1 interrupt custom code
    // or set custom function using PC1_SetInterruptHandler()
}
/**
  Allows selecting an interrupt handler for PD1 at application runtime
*/
void PD1_SetInterruptHandler(void (* interruptHandler)(void)) 
{
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
void PD1_DefaultInterruptHandler(void)
{
    // add your PD1 interrupt custom code
    // or set custom function using PD1_SetInterruptHandler()
}
/**
  Allows selecting an interrupt handler for PD2 at application runtime
*/
void PD2_SetInterruptHandler(void (* interruptHandler)(void)) 
{
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
void PD2_DefaultInterruptHandler(void)
{
    // add your PD2 interrupt custom code
    // or set custom function using PD2_SetInterruptHandler()
}
/**
  Allows selecting an interrupt handler for PD3 at application runtime
*/
void PD3_SetInterruptHandler(void (* interruptHandler)(void)) 
{
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
void PD3_DefaultInterruptHandler(void)
{
    // add your PD3 interrupt custom code
    // or set custom function using PD3_SetInterruptHandler()
}
/**
  Allows selecting an interrupt handler for PA3 at application runtime
*/
void PA3_SetInterruptHandler(void (* interruptHandler)(void)) 
{
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
void PA3_DefaultInterruptHandler(void)
{
    // add your PA3 interrupt custom code
    // or set custom function using PA3_SetInterruptHandler()
}
/**
  Allows selecting an interrupt handler for PA2 at application runtime
*/
void PA2_SetInterruptHandler(void (* interruptHandler)(void)) 
{
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
void PA2_DefaultInterruptHandler(void)
{
    // add your PA2 interrupt custom code
    // or set custom function using PA2_SetInterruptHandler()
}
/**
  Allows selecting an interrupt handler for PC0 at application runtime
*/
void PC0_SetInterruptHandler(void (* interruptHandler)(void)) 
{
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
void PC0_DefaultInterruptHandler(void)
{
    // add your PC0 interrupt custom code
    // or set custom function using PC0_SetInterruptHandler()
}
/**
  Allows selecting an interrupt handler for PA1 at application runtime
*/
void PA1_SetInterruptHandler(void (* interruptHandler)(void)) 
{
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
void PA1_DefaultInterruptHandler(void)
{
    // add your PA1 interrupt custom code
    // or set custom function using PA1_SetInterruptHandler()
}
/**
  Allows selecting an interrupt handler for PA0 at application runtime
*/
void PA0_SetInterruptHandler(void (* interruptHandler)(void)) 
{
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
void PA0_DefaultInterruptHandler(void)
{
    // add your PA0 interrupt custom code
    // or set custom function using PA0_SetInterruptHandler()
}
/**
  Allows selecting an interrupt handler for PD6 at application runtime
*/
void PD6_SetInterruptHandler(void (* interruptHandler)(void)) 
{
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
void PD6_DefaultInterruptHandler(void)
{
    // add your PD6 interrupt custom code
    // or set custom function using PD6_SetInterruptHandler()
}
/**
  Allows selecting an interrupt handler for PF6 at application runtime
*/
void PF6_SetInterruptHandler(void (* interruptHandler)(void)) 
{
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
void PF6_DefaultInterruptHandler(void)
{
    // add your PF6 interrupt custom code
    // or set custom function using PF6_SetInterruptHandler()
}
ISR(PORTA_PORT_vect)
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
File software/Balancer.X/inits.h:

/* 
 * 
 * 
 *
 * 
 */

#ifndef INITS_H
#define	INITS_H

void Global_Init(void);

#define PWM_DISCHARGE_BATTERY  PORTCbits.RC0
#define PWM_CHARGE_BATTERY     PORTCbits.RC1

#define BALANCE_BATT_12V_ON   PORTBbits.RB4=0
#define BALANCE_BATT_12V_OFF  PORTBbits.RB4=1

#define BALANCE_BATT_24V_ON   PORTBbits.RB5=0
#define BALANCE_BATT_24V_OFF  PORTBbits.RB5=1


#define STATUS_LED_D19_ON       PORTBbits.RB2=1
#define STATUS_LED_D19_OFF      PORTBbits.RB2=0

#define STATUS_LED_D18_ON       PORTBbits.RB3=1
#define STATUS_LED_D18_OFF      PORTBbits.RB3=0

#define STATUS_LED_D21_ON       PORTBbits.RB6=1
#define STATUS_LED_D21_OFF      PORTBbits.RB6=0

#define STATUS_LED_D20_ON       PORTBbits.RB7=1
#define STATUS_LED_D20_OFF      PORTBbits.RB7=0

#define STATUS_LED_D23_ON       PORTCbits.RC0=1
#define STATUS_LED_D23_OFF      PORTCbits.RC0=0


#define STATUS_LED_D5_ON       PORTAbits.RA6=1
#define STATUS_LED_D5_OFF      PORTAbits.RA6=0

#endif	/* INITS_H */

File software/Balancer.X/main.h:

/* 
 * 
 * 
 *
 * 
 */

#ifndef DEFINE_H
#define	DEFINE_H

#define _XTAL_FREQ 8000000

#pragma config FOSC = INTRC_NOCLKOUT// Oscillator Selection bits (INTOSCIO oscillator: I/O function on RA6/OSC2/CLKOUT pin, I/O function on RA7/OSC1/CLKIN)
#pragma config WDTE = OFF       // Watchdog Timer Enable bit (WDT disabled and can be enabled by SWDTEN bit of the WDTCON register)
#pragma config PWRTE = OFF      // Power-up Timer Enable bit (PWRT disabled)
#pragma config MCLRE = ON       // RE3/MCLR pin function select bit (RE3/MCLR pin function is MCLR)
#pragma config CP = OFF         // Code Protection bit (Program memory code protection is disabled)
#pragma config CPD = OFF        // Data Code Protection bit (Data memory code protection is disabled)
#pragma config BOREN = OFF      // Brown Out Reset Selection bits (BOR disabled)
#pragma config IESO = OFF       // Internal External Switchover bit (Internal/External Switchover mode is disabled)
#pragma config FCMEN = OFF      // Fail-Safe Clock Monitor Enabled bit (Fail-Safe Clock Monitor is disabled)
#pragma config LVP = OFF        // Low Voltage Programming Enable bit (RB3 pin has digital I/O, HV on MCLR must be used for programming)

// CONFIG2
#pragma config BOR4V = BOR40V   // Brown-out Reset Selection bit (Brown-out Reset set to 4.0V)
#pragma config WRT = OFF        // Flash Program Memory Self Write Enable bits (Write protection off)



#endif	/* DEFINE_H */

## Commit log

2024-08-19 Initial commit with project files: PCB design in KiCad and documentation
2024-08-19 Routing display and probe
2024-08-20 Display pcb routing
2024-08-21 Add first concept of tl494 power supply
2024-08-22 Update schematic for ESP32, split schematic sheets
2024-08-23 Add lcd display spi schematic, update tl494 boost converter
2024-08-26 Ideal diode + buck
2024-08-26 bi-directional smps concept
2024-08-27 Fix bugs
2024-08-28 Add bidirectional smps concept, split bms schematic
2024-08-30 add simulations, split bms and esp schematics
2024-08-30 Add simulations and recheck schematics + cleanup
2024-09-03 Add aditional 7 segment displays
2024-09-03 Chceck and update DC module and meter probe pcb
2024-09-03 MPPT LT3652 schematic uptade
2024-09-04 Add TL494 simulation
2024-09-05 lt3252 circut simulation and update schematic
2024-09-09 part placement of bms pcb
2024-09-09 Routing balancer pcb
2024-09-09 add spliter
2024-09-11 Splitter PCB, connectors esp board
2024-09-13 Gas sensor circuit improvement
2024-09-15 Balancer PCB parts positions
2024-09-16 Splitters
2024-09-18 Splitter and connector footprints, progress with balancer pcb routing
2024-09-19 balancer pcb progress
2024-09-19 splitter components adjustment
2024-09-20 Route balancer progress
2024-09-22 Balancer routing
2024-09-24 PCB UPDATE
2024-09-25 PCB footprint changes
2024-09-27 Update of ESP32 PCB - parts positioning
2024-09-29 esp pcb
2024-09-30 Routing PCB
2024-10-01 ESP PCB Route progress
2024-10-01 esp pcb route
2024-10-02 corase routing for esp doce
2024-10-02 Fineing ESP PCB
2024-10-02 change relay
2024-10-03 ESP relay circut change
2024-10-03 Change MAX232 to MAX3232
2024-10-04 Add misc shift register for display schematic, ideal bridge and sd card switcher
2024-10-06 add misc board schematic
2024-10-07 Add SD card switcher circuit, some changes in pcb and schematic
2024-10-07 add power tracking heater
2024-10-08 progress with esp power pcb
2024-10-09 Shift register for LCD update
2024-10-09 add footprint association
2024-10-10 update power tracking heater
2024-10-14 Parts chage for bms
2024-10-14 power tracking heater progress
2024-10-14 power tracking heater update
2024-10-16 update of power tracking heater
2024-10-17 Power tracking heater done
2024-10-17 kicad oc
2024-10-18 LT3625 pcb
2024-10-20 done LT3652
2024-10-23 clean up, some minor changes
2024-10-24 Bidirectional DC - change shunt resistor
2024-10-28 Drawning schematic for buck/boost converter
2024-10-29 add production files
2024-10-30 Schematic for buck/boost conv
2024-10-31 buck boost conv. progrress
2024-11-03 buck-boost conv update
2024-11-04 buck boost progress
2024-11-05 ocnv
2024-11-05 boost converter xl6019 schematic
2024-11-07 XL smps pcb routing
2024-11-08 routing pcb smps
2024-11-11 Add first sw project for balancer, add new revision of balancer pcb
2024-11-13 Balancer - AVR version
2024-11-14 change uc on balancer
2024-11-14 INA working
2024-11-14 adc working on
2024-11-17 balancer code - balancing 12v batt, apply .gitignore rules
2024-11-29 Balancer-AVR-source
2024-12-01 change with balancer schematic, generate code for avr
2024-12-02 ADD INA PROTECTION
2024-12-07 Add 3D PCB view
2024-12-24 values update
2025-03-10 add ADC code
2025-03-10 Update gitignore
2025-03-16 update balancer ina code
2025-03-17 I2C working along with INA
2025-03-31 Add PWM code
2025-04-03 readme update
2025-04-03 Add photos from PV mouting structure
2025-04-13 New schematic BMS
2025-04-14 Add electrical schematic
2025-04-15 New version of balancer PCB and schematic
2025-04-15 Add PWM TCD4 for Balancer
2025-04-22 update balancer schematic
2025-04-23 Update electrical schematic and BMS schematic
2025-04-24 Update electrical schematic
2025-04-28 Update electrical schematic and readme
2025-05-04 Change PWM frequency to 25kHz
2025-05-05 Add different driver simulations
2025-05-06 Balancer PCB update
2025-05-07 Balancer PCB routing
2025-05-07 First working balancer
2025-05-08 add P-regulator test code
2025-05-08 P-type regulator working
2025-05-09 Add soft-start for balancer
2025-05-12 Add differential opamp ltspice simulation
2025-05-12 Balancer P-regulator code update
2025-05-15 update balancer code and add thermistor measurment
2025-05-16 Temperature regualtor
2025-05-18 Regulator update
2025-05-20 update balancer pcb - add gnd vdrop opamp
2025-05-22 update pid
2025-05-22 pid regulator working first time
2025-05-23 Clean up,, add data struct and printf debug functions
2025-05-26 add nanomodbus lib
2025-05-26 balance cells pid progress
2025-05-27 nanomodbus lib integration in progress
2025-06-05 Update balacer schematic - change fan drive circuit, fix current limiter drive
2025-06-05 mmc pinout update, change schematic
2025-06-09 balacer routing update
2025-06-10 update balancer pcb
2025-06-11 balancer routing done
2025-06-12 add tca0 configuration
2025-06-13 balancer pcb change smps diode footprint, schematic cleanup, designators arrangement, add mouting holes
2025-06-27 add esp32 master modbus setup
2025-06-29 esp32 modbus easun working
2025-06-30 Move modbus request to separate file
2025-07-01 update esp32 easun modbus
2025-07-04 add esp32 master esphome config
2025-07-07 esp32 update
2025-07-07 working esphome with easun
2025-07-09 sol/uti for low pv voltage done
2025-07-09 add power switching output priority for easun
2025-07-09 add easun power logic
2025-07-15 update mode logic
2025-08-05 update easun logic, add ntc thermistor data
2025-08-06 add iec62056 component
2025-08-06 add elevation angle component, remove energy meter logic
2025-08-08 add meter probe esp32 test config
2025-08-12 add modbus meter test
2025-08-29 add serialmodbus
2025-08-31 pozyton esphome component
2025-08-31 working code with pozyton eabm
2025-08-31 add validation
2025-09-01 epshome sensor in progrress
2025-09-01 add sensor python and publish functions
2025-09-02 add register_component functions and cast class variables
2025-09-02 publish_measurmet compiled
2025-09-04 add sp32 new schematic version
2025-09-04 esp32 schematic update
2025-09-05 add esp32 pcb connectors and logic translators
2025-09-07 esp32 master update
2025-09-08 esp master v2.0 routing progress
2025-09-09 done routing esp32 master
2025-09-10 add refrence cell schematic
2025-09-11 add refrence cell pcb
2025-09-15 add balancer power module
2025-09-21 add bms pcb balacer and smps separated
2025-10-05 Add application notes
2025-10-14 routing power module
2025-10-14 update power pcb
2025-10-15 done PCB power module and balancer
2025-10-16 Done balancer and current limiter pcb, other pcb cleanup
2025-11-02 fix pcb esp32 master, change esphome pinout
2025-11-13 add simulation
2025-11-21 add obis codes
